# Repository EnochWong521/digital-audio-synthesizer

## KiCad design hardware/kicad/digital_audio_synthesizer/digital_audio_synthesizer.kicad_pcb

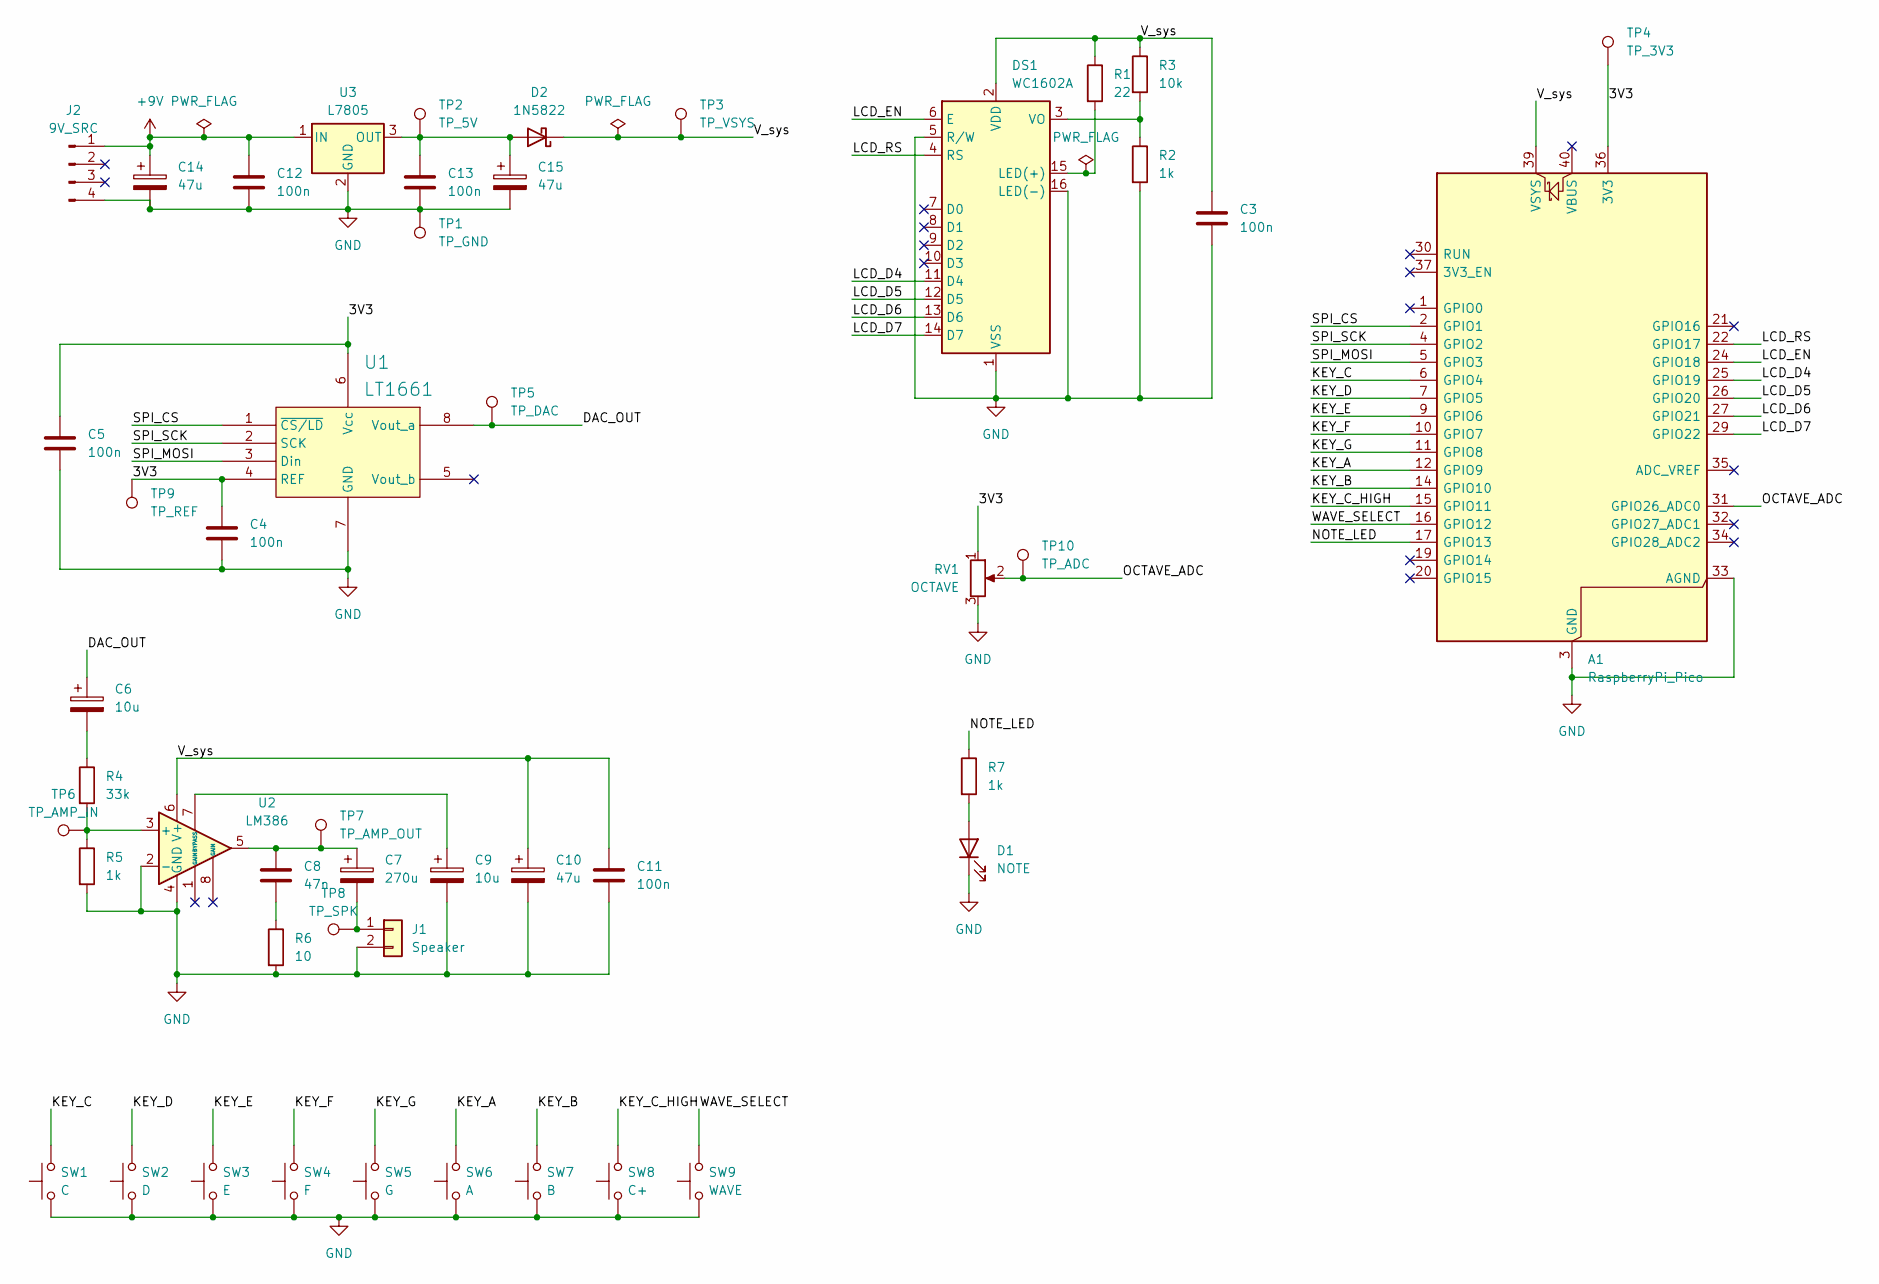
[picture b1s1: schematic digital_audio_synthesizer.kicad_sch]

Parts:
A1: RaspberryPi_Pico; RaspberryPi_Pico_Common_THT
C3, C4, C5, C11, C12, C13: 100n; C_Disc_D5.0mm_W2.5mm_P5.00mm
C6, C9: 10u; CP_Radial_D5.0mm_P2.50mm
C7: 270u; CP_Radial_D8.0mm_P3.50mm
C8: 47n; C_Disc_D3.8mm_W2.6mm_P2.50mm
C10, C14, C15: 47u; CP_Radial_D5.0mm_P2.50mm
D1: NOTE; LED_D5.0mm
D2: 1N5822; D_DO-201AD_P15.24mm_Horizontal
DS1: WC1602A
J1: Speaker; PinHeader_1x02_P2.54mm_Vertical
J2: 9V_SRC; PinHeader_1x04_P2.54mm_Vertical
R1: 22; R_Axial_DIN0204_L3.6mm_D1.6mm_P7.62mm_Horizontal
R2, R5, R7: 1k; R_Axial_DIN0207_L6.3mm_D2.5mm_P7.62mm_Horizontal
R3: 10k; R_Axial_DIN0207_L6.3mm_D2.5mm_P7.62mm_Horizontal
R4: 33k; R_Axial_DIN0207_L6.3mm_D2.5mm_P7.62mm_Horizontal
R6: 10; R_Axial_DIN0207_L6.3mm_D2.5mm_P7.62mm_Horizontal
RV1: OCTAVE; Potentiometer_Piher_PT-10-V10_Vertical
SW1: C; SW_PUSH_6mm_H4.3mm
SW2: D; SW_PUSH_6mm_H4.3mm
SW3: E; SW_PUSH_6mm_H4.3mm
SW4: F; SW_PUSH_6mm_H4.3mm
SW5: G; SW_PUSH_6mm_H4.3mm
SW6: A; SW_PUSH_6mm_H4.3mm
SW7: B; SW_PUSH_6mm_H4.3mm
SW8: C+; SW_PUSH_6mm_H4.3mm
SW9: WAVE; SW_PUSH_6mm_H4.3mm
TP1: TP_GND; TestPoint_THTPad_D2.0mm_Drill1.0mm
TP2: TP_5V; TestPoint_THTPad_D2.0mm_Drill1.0mm
TP3: TP_VSYS; TestPoint_THTPad_D2.0mm_Drill1.0mm
TP4: TP_3V3; TestPoint_THTPad_D2.0mm_Drill1.0mm
TP5: TP_DAC; TestPoint_THTPad_D2.0mm_Drill1.0mm
TP6: TP_AMP_IN; TestPoint_THTPad_D2.0mm_Drill1.0mm
TP7: TP_AMP_OUT; TestPoint_THTPad_D2.0mm_Drill1.0mm
TP8: TP_SPK; TestPoint_THTPad_D2.0mm_Drill1.0mm
TP9: TP_REF; TestPoint_THTPad_D2.0mm_Drill1.0mm
TP10: TP_ADC; TestPoint_THTPad_D2.0mm_Drill1.0mm
U1: LT1661; DIP-8_W7.62mm
U2: LM386; DIP-8_W7.62mm
U3: L7805; TO-220-3_Vertical

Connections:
+9V: C12.1, C14.1, J2.1, U3.1 (IN)
/3V3: A1.36 (3V3), C4.1, C5.1, RV1.1, TP4.1 (1_1), TP9.1 (1_1), U1.4 (REF), U1.6 (Vcc)
/DAC_OUT: C6.1, TP5.1 (1_1), U1.8 (Vout_a)
/KEY_A: A1.12 (GPIO9), SW6.2
/KEY_B: A1.14 (GPIO10), SW7.2
/KEY_C: A1.6 (GPIO4), SW1.2
/KEY_C_HIGH: A1.15 (GPIO11), SW8.2
/KEY_D: A1.7 (GPIO5), SW2.2
/KEY_E: A1.9 (GPIO6), SW3.2
/KEY_F: A1.10 (GPIO7), SW4.2
/KEY_G: A1.11 (GPIO8), SW5.2
/LCD_D4: A1.25 (GPIO19), DS1.11 (D4)
/LCD_D5: A1.26 (GPIO20), DS1.12 (D5)
/LCD_D6: A1.27 (GPIO21), DS1.13 (D6)
/LCD_D7: A1.29 (GPIO22), DS1.14 (D7)
/LCD_EN: A1.24 (GPIO18), DS1.6 (E)
/LCD_RS: A1.22 (GPIO17), DS1.4 (RS)
/NOTE_LED: A1.17 (GPIO13), R7.1
/OCTAVE_ADC: A1.31 (GPIO26_ADC0), RV1.2, TP10.1 (1_1)
/SPI_CS: A1.2 (GPIO1), U1.1 (~CS/LD)
/SPI_MOSI: A1.5 (GPIO3), U1.3 (Din)
/SPI_SCK: A1.4 (GPIO2), U1.2 (SCK)
/V_sys: A1.39 (VSYS), C3.1, C10.1, C11.1, D2.1 (K), DS1.2 (VDD), R1.1, R3.1, TP3.1 (1_1), U2.6 (V+)
/WAVE_SELECT: A1.16 (GPIO12), SW9.2
GND: A1.3 (GND), A1.8 (GND), A1.13 (GND), A1.18 (GND), A1.23 (GND), A1.28 (GND), A1.33 (AGND), A1.38 (GND), C3.2, C4.2, C5.2, C9.2, C10.2, C11.2, C12.2, C13.2, C14.2, C15.2, D1.1 (K), DS1.1 (VSS), DS1.5 (R/W), DS1.16 (LED(-)), J1.2, J2.4, R2.2, R5.2, R6.2, RV1.3, SW1.1, SW2.1, SW3.1, SW4.1, SW5.1, SW6.1, SW7.1, SW8.1, SW9.1, TP1.1 (1_1), U1.7 (GND), U2.2 (-), U2.4 (GND), U3.2 (GND)
unnamed: C6.2, R4.1
unnamed: C7.1, C8.1, TP7.1 (1_1), U2.5
unnamed: C8.2, R6.1
unnamed: D1.2 (A), R7.2
unnamed: C13.1, C15.1, D2.2 (A), TP2.1 (1_1), U3.3 (OUT)
unnamed: DS1.15 (LED(+)), R1.2
unnamed: DS1.3 (VO), R2.1, R3.2
unnamed: C7.2, J1.1, TP8.1 (1_1)
unnamed: R4.2, R5.1, TP6.1 (1_1), U2.3 (+)
unnamed: C9.1, U2.7 (BYPASS)

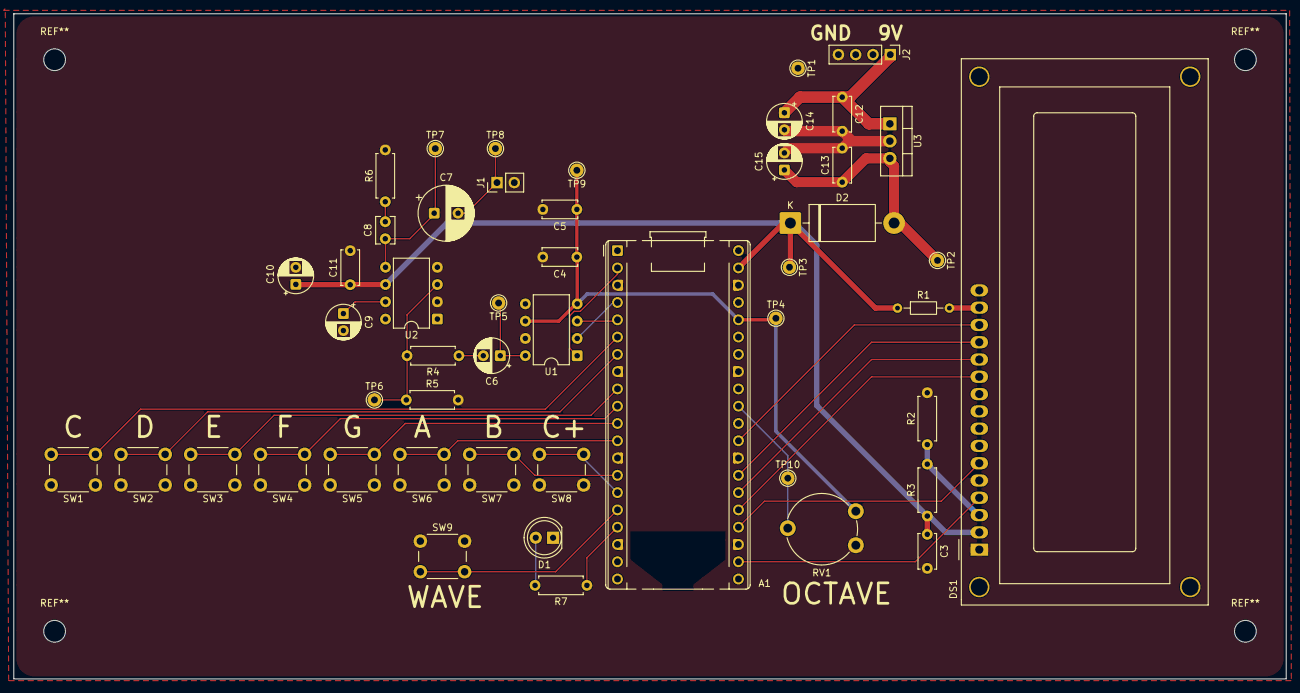
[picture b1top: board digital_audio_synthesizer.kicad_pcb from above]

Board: 2 copper layers, 187.0 x 97.8 mm, 49 parts (0 on the bottom side), 35 nets.

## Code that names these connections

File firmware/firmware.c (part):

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#define DAC_MOSI     3

#define WAVE_BUTTON  12
#define OCTAVE_ADC   26

#define LCD_RS       17
#define LCD_EN       18
#define LCD_D4       19
#define LCD_D5       20
#define LCD_D6       21
#define LCD_D7       22

#define NOTE_LED_PIN 13

static const uint NOTE_PINS[8] = {
    4, 5, 6, 7, 8, 9, 10, 11
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// ========================================

static void lcd_nibble(uint8_t value) {
    gpio_put(LCD_D4, (value >> 0) & 1);
    gpio_put(LCD_D5, (value >> 1) & 1);
    gpio_put(LCD_D6, (value >> 2) & 1);
    gpio_put(LCD_D7, (value >> 3) & 1);

    sleep_us(1);
    gpio_put(LCD_EN, 1);
    sleep_us(2);
    gpio_put(LCD_EN, 0);
    sleep_us(2);
}

static void lcd_byte(uint8_t value, bool data) {
    gpio_put(LCD_RS, data ? 1 : 0);

    lcd_nibble(value >> 4);
    lcd_nibble(value & 0x0F);
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    }

    adc_init();
    adc_gpio_init(OCTAVE_ADC);
    adc_select_input(0);

    lcd_init();
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            atomic_store(&audio_active, note >= 0);

            // Digital output: LED ON when a note is pressed
            gpio_put(NOTE_LED_PIN, note >= 0);

            char line1[17];
            char line2[17];
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    
    init_dac();

    gpio_init(NOTE_LED_PIN);
    gpio_set_dir(NOTE_LED_PIN, GPIO_OUT);
    gpio_put(NOTE_LED_PIN, 0);

    multicore_launch_core1(controls_core);

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
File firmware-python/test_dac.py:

from machine import Pin, SPI
from time import sleep

# Same SPI configuration as previous lab
SPI_CS_PIN = 1
SPI_SCK_PIN = 2
SPI_MOSI_PIN = 3

spi = SPI(
    0,
    baudrate=1_000_000,
    polarity=0,
    phase=0,
    sck=Pin(SPI_SCK_PIN),
    mosi=Pin(SPI_MOSI_PIN)
)

cs = Pin(SPI_CS_PIN, Pin.OUT, value=1)

buf = bytearray(2)


def write_dac(value):
    value = max(0, min(1023, value))

    # Original lab command: update both DACs
    word = (0b1111 << 12) | (value << 2)

    buf[0] = (word >> 8) & 0xFF
    buf[1] = word & 0xFF

    cs.value(0)
    spi.write(buf)
    cs.value(1)


# Change this to 256, 512, or 768
DAC_VALUE = 512

write_dac(DAC_VALUE)

print("DAC output set to:", DAC_VALUE)

# Hold the output without additional SPI activity
while True:
    sleep(1)
